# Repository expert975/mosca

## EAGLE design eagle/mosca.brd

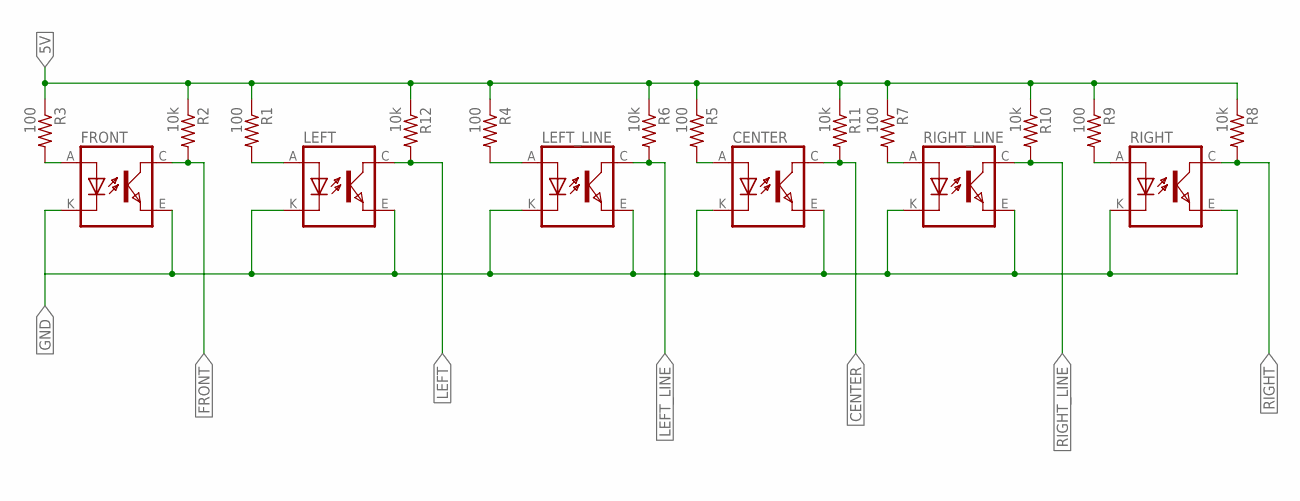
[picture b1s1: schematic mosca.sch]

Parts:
CENTER: TCRT5000
FRONT: TCRT5000
LEFT: TCRT5000
LEFT_LINE: TCRT5000
R1, R3, R4, R5, R7, R9: 100; 0204/7
R2, R6, R8, R10, R11, R12: 10k; 0204/7
RIGHT: TCRT5000
RIGHT_LINE: TCRT5000

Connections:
5V: R1.1, R2.1, R3.1, R4.1, R5.1, R6.1, R7.1, R8.1, R9.1, R10.1, R11.1, R12.1
CENTER: CENTER.C (COLLECTOR), R11.2
FRONT: FRONT.C (COLLECTOR), R2.2
GND: CENTER.E (EMITTER), CENTER.K (CATHODE), FRONT.E (EMITTER), FRONT.K (CATHODE), LEFT.E (EMITTER), LEFT.K (CATHODE), LEFT_LINE.E (EMITTER), LEFT_LINE.K (CATHODE), RIGHT.E (EMITTER), RIGHT.K (CATHODE), RIGHT_LINE.E (EMITTER), RIGHT_LINE.K (CATHODE)
LEFT: LEFT.C (COLLECTOR), R12.2
LEFT_LINE: LEFT_LINE.C (COLLECTOR), R6.2
unnamed: LEFT_LINE.A (ANODE), R4.2
unnamed: LEFT.A (ANODE), R1.2
unnamed: CENTER.A (ANODE), R5.2
unnamed: R7.2, RIGHT_LINE.A (ANODE)
unnamed: R9.2, RIGHT.A (ANODE)
unnamed: FRONT.A (ANODE), R3.2
RIGHT: R8.2, RIGHT.C (COLLECTOR)
RIGHT_LINE: R10.2, RIGHT_LINE.C (COLLECTOR)

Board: 2 copper layers, 18 parts (0 on the bottom side), 14 nets, no tracks yet.

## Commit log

2017-07-01 Initialize PlataformIO project
2017-07-01 Add main source file
2017-07-03 Add sensor schematic
2017-07-08 Add sensor testing code
2017-08-25 Add eagle files
2017-08-31 Initial commit
    - Copy code from PID project
    - Begin line follower implementation
2017-08-31 Add L293D lib
2017-08-31 Test sensors and structure code
    - Split code into specialized functions.
    - Start sensor readings.
    - Start debug function.
2017-09-01 Add control variables for engines and debug
2017-09-01 Add followingLine control variable
    - Assemble PID calculation function.
2017-09-01 Implemente modusOperandi
2017-09-01 Enable debug and engines
2017-09-01 Structure mode setup
2017-09-01 Add PID tu debug
2017-09-01 Rename engine constant to ENABLE_ENGINES
2017-09-01 Update control
2017-09-01 Add Ultrasonic library
2017-09-01 Define ultrasonics
2017-09-02 Implement open loop moves
2017-09-02 Implement open loop procedures
    - Implement claw and backdoor movements
    - Implement ball seek
2017-09-02 Add Servo library
2017-09-02 I tried
